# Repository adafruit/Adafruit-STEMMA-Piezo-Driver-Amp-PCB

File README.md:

## Adafruit STEMMA Piezo Driver Amp - PAM8904 PCB

<a href="http://www.adafruit.com/products/5791"><br/>
Click here to purchase one from the Adafruit shop</a>

PCB files for the Adafruit STEMMA Piezo Driver Amp - PAM8904. 

Format is EagleCAD schematic and board layout
* https://www.adafruit.com/product/5791

### Description

Piezos make noise when you put an AC voltage across them: and the bigger the Vpp the louder they are. With your standard 3V logic microcontroller you can make 3Vpp with a PWM out, or 6Vpp differential with two complimentary outputs. But what if you want even louder? Or if you're using a piezo to sense distance using ultrasonic bounces?

We found the nifty PAM8904, which is an amplifier specifically designed for driving piezo elements - and unlike audio amplifiers it's good for up to 300 KHz! It's a switched-cap piezo driver that has bridge-tied load (BTL) output and up to 3x voltage multiplication thanks to a built in boosting circuit for up to ~13Vpp.

We whipped up a quick breakout in our 2mm JST-PH STEMMA form-factor to make it easy for anyone who wants to beep their boops very loudly. 

Usage is easy: power with 3 to 5VDC on the Vin and GND pins. Then provide a square wave on the signal pin, from 20Hz to 300KHz - any duty cycle is ok but 50% will probably work best. Theres a dual DIP switch to set the gain: you can set it to off (zero gain), x1 gain, x2 gain and x3 gain. The output is differential so 2x gain will give you 4xVin peak-to-peak across the piezo lines. Connect your piezo to the terminal block and you're ready to rock. 

Please note: If you are powering the driver from 5VDC, don't set the gain to x3 because the 15V output is higher than the driver is specified for. (Yeah we also sorta wondered why the chip manufacturer allows it). So if you are using 3.3V power, x3 gain is OK and will give you about 10V out but if you're powering with 5V use 2x gain max to keep the max voltage at 10V.

Piezo element and 3-pin JST PH cable not included! But we stock em in the shop if you want to pick up separately.

### License

Adafruit invests time and resources providing this open source design, please support Adafruit and open-source hardware by purchasing products from [Adafruit](https://www.adafruit.com)!

Designed by Limor Fried/Ladyada for Adafruit Industries.

Creative Commons Attribution/Share-Alike, all text above must be included in any redistribution. 
See license.txt for additional details.

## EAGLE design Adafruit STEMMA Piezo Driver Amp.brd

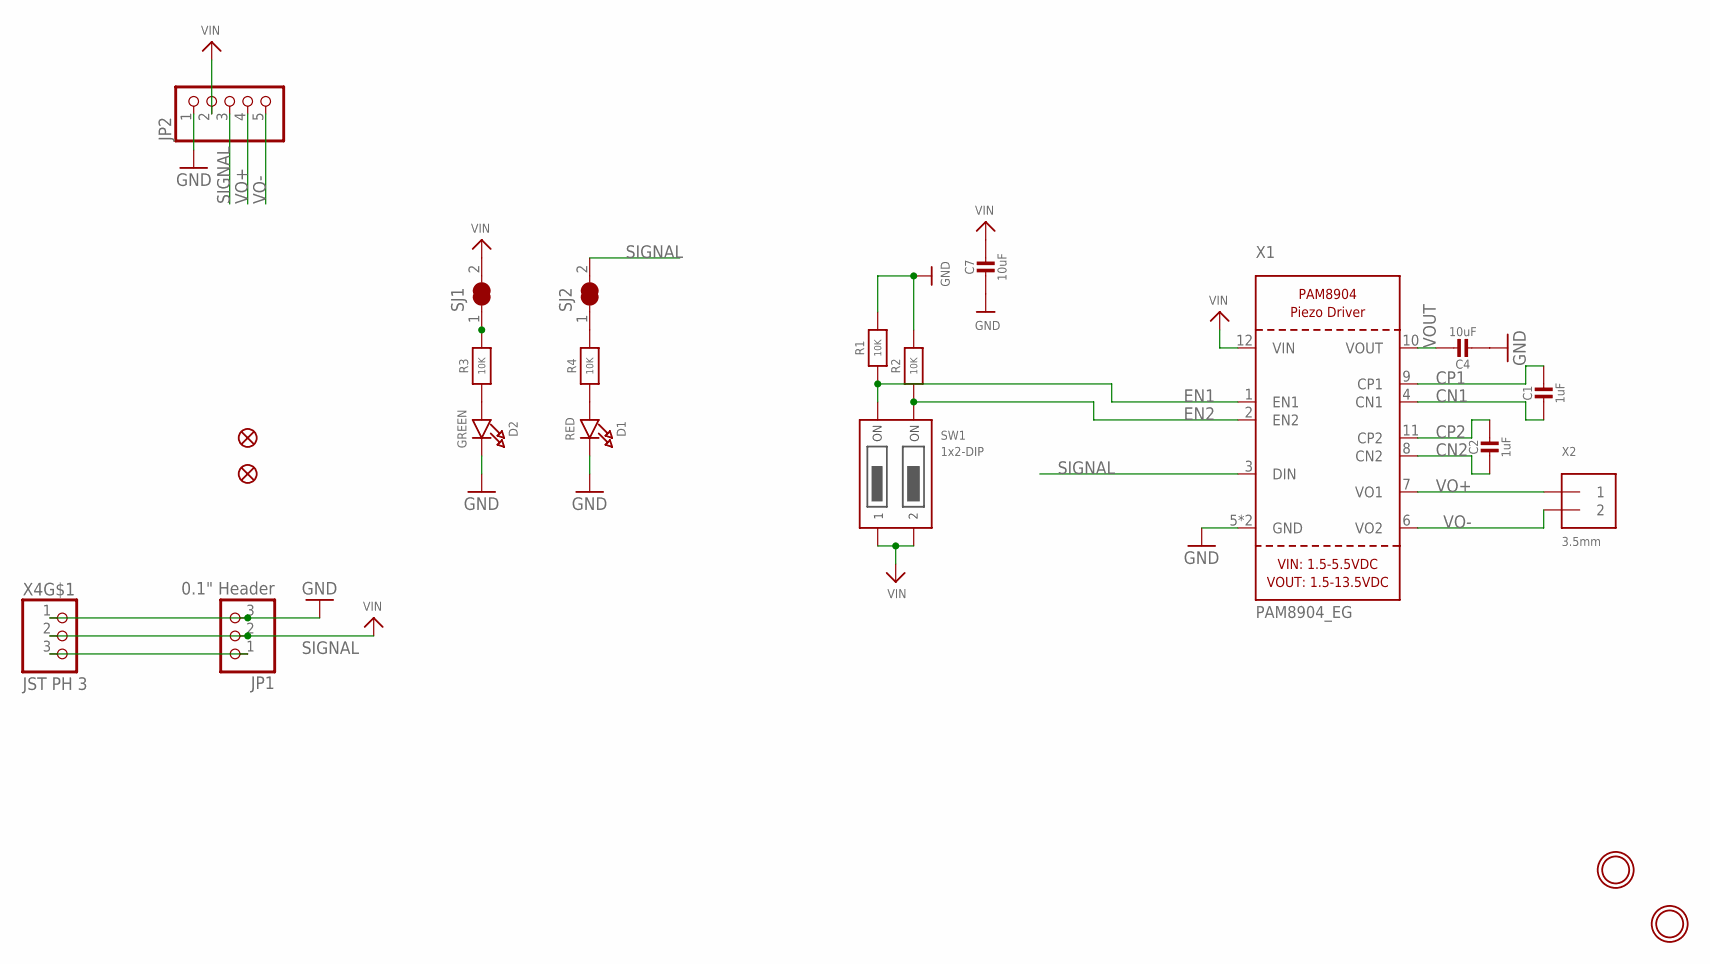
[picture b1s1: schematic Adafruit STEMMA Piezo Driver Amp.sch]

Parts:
C1, C2: 1uF; 0603-NO
C4, C7: 10uF; 0805-NO
D1: RED; CHIPLED_0603_NOOUTLINE
D2: GREEN; CHIPLED_0603_NOOUTLINE
FID2, FID3: FIDUCIAL_1MM
JP1: 0.1" Header; 1X03_OVAL
JP2: HEADER-1X570MIL; 1X05_ROUND_70
R1, R2, R3, R4: 10K; 0603-NO
SJ1, SJ2: SOLDERJUMPER_CLOSED; SOLDERJUMPER_CLOSEDWIRE
SW1: 1x2-DIP; DIPSWITCH_2PIN
U$1, U$8: MOUNTINGHOLE2.5; MOUNTINGHOLE_2.5_PLATED
X1: PAM8904_EG; QFN12-2MM
X2: 3.5mm; TERMBLOCK_1X2-3.5MM
X4: JST PH 3; JSTPH3

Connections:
CN1: C1.2, X1.4 (CN1)
CN2: C2.2, X1.8 (CN2)
CP1: C1.1, X1.9 (CP1)
CP2: C2.1, X1.11 (CP2)
EN1: R1.1, SW1.1ON, X1.1 (EN1)
EN2: R2.1, SW1.2ON, X1.2 (EN2)
GND: C4.2, C7.2, D1.C, D2.C, JP1.3, JP2.1, R1.2, R2.2, X1.5 (GND), X1.MT (GND), X4.1
unnamed: R3.2, SJ1.1
unnamed: D1.A, R4.1
unnamed: R4.2, SJ2.1
unnamed: D2.A, R3.1
SIGNAL: JP1.1, JP2.3, SJ2.2, X1.3 (DIN), X4.3
VIN: C7.1, JP1.2, JP2.2, SJ1.2, SW1.1OFF, SW1.2OFF, X1.12 (VIN), X4.2
VO+: JP2.4, X1.7 (VO1), X2.1
VO-: JP2.5, X1.6 (VO2), X2.2
VOUT: C4.1, X1.10 (VOUT)

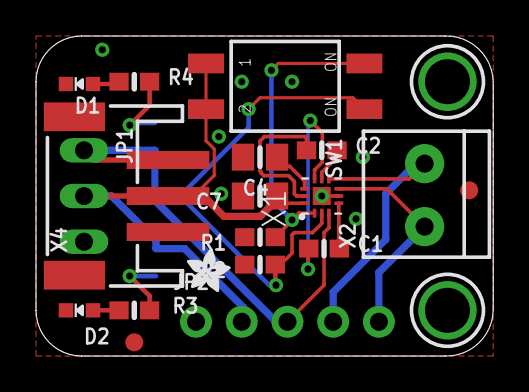
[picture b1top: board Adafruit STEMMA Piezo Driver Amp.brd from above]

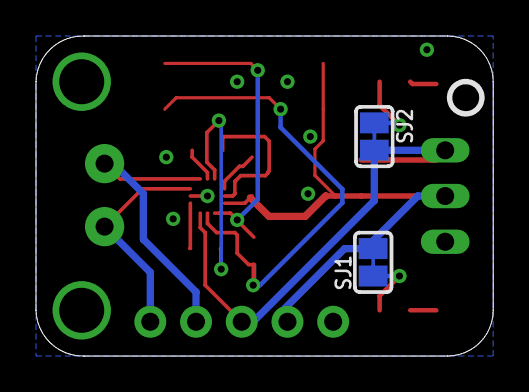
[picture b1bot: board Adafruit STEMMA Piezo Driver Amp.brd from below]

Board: 2 copper layers, 25.4 x 17.8 mm, 38 parts (11 on the bottom side), 16 nets.

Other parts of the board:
PLABEL0: PLABEL0
PLABEL7: PLABEL7
PLABEL8: PLABEL8
PLABEL10: PLABEL10
PLABEL11: PLABEL11
PLABEL12: PLABEL12
PLABEL13: PLABEL13
PLABEL14: PLABEL14
PLABEL15: PLABEL15
PLABEL16: PLABEL16
PLABEL17: PLABEL17
PLABEL18: PLABEL18
PLABEL19: PLABEL19
PLABEL20: PLABEL20
U$5: PCBFEAT-REV-040
U$19: ADAFRUIT_2.5MM

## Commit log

2023-09-05 adding cookiecutter output

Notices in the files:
parts and their libraries:
microbuilder: This work is placed in the public domain, and may be freely used for commercial and non-commercial work with the following conditions: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
